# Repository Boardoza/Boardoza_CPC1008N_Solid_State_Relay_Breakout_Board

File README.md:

# Boardoza CPC1008N Solid State Relay Breakout Board

The **Boardoza CPC1008N Solid State Relay Breakout Board** is designed to provide safe, silent, and reliable switching for low-power **AC and DC loads** in maker and embedded projects. Based on the **CPC1008N Solid State Relay (SSR)**, it supports up to **100 Vp blocking voltage**, **150 mA continuous load current**, and offers **1500 Vrms optical isolation** between the input and output, ensuring dependable performance and improved system safety.

With its compact and efficient design, this breakout board is well suited for applications such as **multiplexers, data acquisition systems, electronic switching, I/O subsystems, and utility meters (electricity, water, and gas)**. It is also widely used in **medical devices, security systems, and industrial automation projects**, making it a modern, maintenance-free alternative to traditional reed relays for both hobbyists and professional developers.

## [Click here to purchase!](https://www.ozdisan.com/ureticiler/boardoza)

| Front Side | Back Side |
|:---:|:---:|
|  |  |

---

## Key Features

- **Solid State Relay (SSR):** Provides safe, silent, and reliable switching for low-power AC and DC loads.
- **AC/DC Output Support:** Suitable for switching both alternating and direct current loads.
- **Optical Isolation:** Ensures electrical isolation between input and output for improved safety.
- **No Mechanical Wear:** Fully electronic switching with no contact bounce or lifetime limitations.
- **Low EMI/RFI:** Generates no electromagnetic or radio frequency interference during operation.

---

## Technical Specifications

**Model:** CPC1008N  
**Manufacturer:** Boardoza  
**Manufacturer IC:** IXYS / Littelfuse  
**Functions:** Solid State Relay (AC/DC Output)  
**Input Control Current:** 50 mA – 1 A  
**Blocking Voltage:** 100 Vp  
**Continuous Load Current:** 150 mA  
**Isolation Voltage:** 1500 Vrms  
**Off-State Leakage Current:** 1 µA @ 100 V  
**Operating Temperature:** -40 °C to +85 °C  
**Board Dimensions:** 20 mm × 20 mm  

---

## Board Pinout

### **( J1 ) Control Input Connector**

| Pin Number | Pin Name | Description |
| :---: | :---: | --- |
| 1 | SIGNAL | Control Input Signal |
| 2 | GND | Ground |

### **( J2 ) Load Output Connector**

| Pin Number | Pin Name | Description |
| :---: | :---: | --- |
| 1 | OUTA | Load Connection |
| 2 | OUTB | Load Connection |

---

## Board Dimensions

---

## Step Files

[Boardoza CPC1008N.step](./assets/CPC1008N%20Step.step)

---

## Datasheet

[CPC1008N Datasheet.pdf](./assets/CPC1008N%20Datasheet.pdf)

---

## Version History

- V1.0.0 – Initial Release

---

## Support

- If you have any questions or need support, please contact **<support@boardoza.com>**

---

## **License**
### **Hardware Design**

[![CC BY-SA 4.0][cc-by-sa-shield]][cc-by-sa]

All hardware design files are licensed under [Creative Commons Attribution-ShareAlike 4.0 International License][cc-by-sa].

[cc-by-sa]: http://creativecommons.org/licenses/by-sa/4.0/
[cc-by-sa-shield]: https://img.shields.io/badge/License-CC%20BY--SA%204.0-lightgrey.svg

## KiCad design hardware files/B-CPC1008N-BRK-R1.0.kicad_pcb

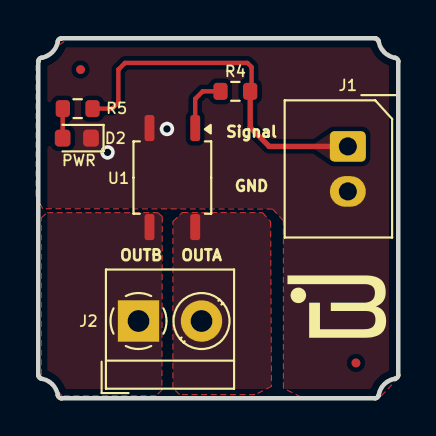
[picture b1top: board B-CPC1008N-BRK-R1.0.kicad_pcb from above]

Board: 2 copper layers, 20.0 x 20.0 mm, 6 parts (0 on the bottom side), 6 nets.

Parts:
D2: LED; LED_0603_1608Metric
J1: Conn_01x02; 2317-02S_1x02_P2.50mm_Vertical
J2: Screw_Terminal_01x02; TerminalBlock_MetzConnect_Type059_RT06302HBWC_1x02_P3.50mm_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
R4: 1k; R_0603_1608Metric
R5: 330; R_0603_1608Metric
U1: CPC1008N; SOP-4_3.8x4.1mm_P2.54mm

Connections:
/Signal: J1.1, R4.2, R5.1
GND: D2.1 (K), J1.2, U1.2
unnamed: D2.2 (A), R5.2
unnamed: J2.1, U1.3
unnamed: J2.2, U1.4
unnamed: R4.1, U1.1
